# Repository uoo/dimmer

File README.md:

# dimmer
Computer controlled 24-channel dimmer

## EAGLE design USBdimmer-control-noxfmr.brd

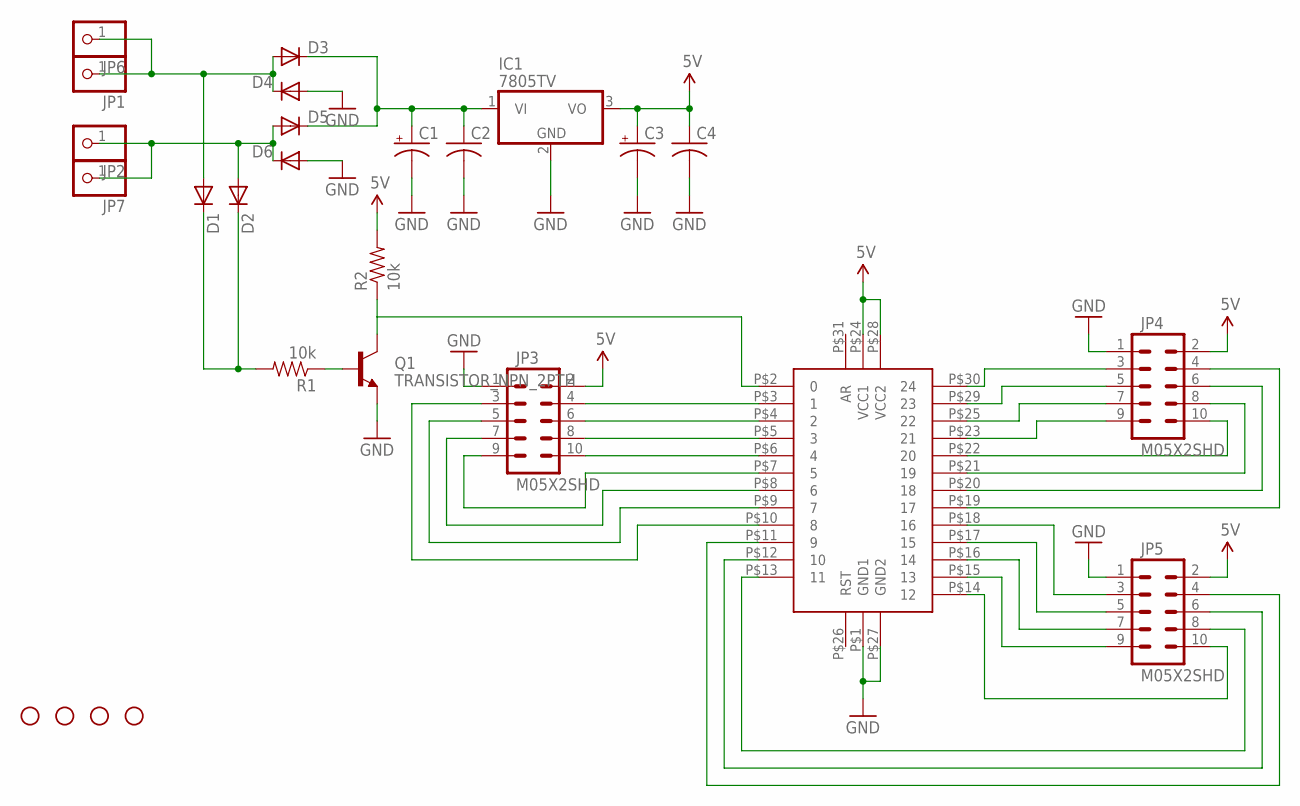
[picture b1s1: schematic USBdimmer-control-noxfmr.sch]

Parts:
C1, C3: CPOL-USE3.5-10; E3,5-10
C2, C4: C-US025-030X050; C025-030X050
D1, D2: DIODE1N4148; DIODE-1N4148
D3, D4, D5, D6: DIODEPTH; DIODE-1N4001
IC1: 7805TV; TO220V
IC2: TEENSY2
JP1, JP2, JP6, JP7: PINHD-1X1; 1X01
JP3, JP4, JP5: M05X2SHD; 2X5-SHROUDED
Q1: TRANSISTOR_NPN_2PTH; TO-92
R1, R2: 10k; AXIAL-0.4
STANDOFF1, STANDOFF2, STANDOFF3, STANDOFF4: STAND-OFF

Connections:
5V: C3.+, C4.1, IC1.3 (VO), IC2.P$24 (VCC1), IC2.P$28 (VCC2), JP3.2, JP4.2, JP5.2, R2.P$2 (2)
GND: C1.-, C2.2, C3.-, C4.2, D4.A, D6.A, IC1.2 (GND), IC2.P$1 (GND1), IC2.P$27 (GND2), JP3.1, JP4.1, JP5.1, Q1.3 (E)
unnamed: D2.A, D5.A, D6.C, JP2.1, JP7.1
unnamed: D1.A, D3.A, D4.C, JP1.1, JP6.1
unnamed: C1.+, C2.1, D3.C, D5.C, IC1.1 (VI)
unnamed: IC2.P$21 (19), JP4.8
unnamed: IC2.P$20 (18), JP4.6
unnamed: Q1.2 (B), R1.P$1 (1)
unnamed: D1.C, D2.C, R1.P$2 (2)
unnamed: IC2.P$2 (0), Q1.1 (C), R2.P$1 (1)
unnamed: IC2.P$19 (17), JP4.4
unnamed: IC2.P$18 (16), JP5.3
unnamed: IC2.P$3 (1), JP3.4
unnamed: IC2.P$4 (2), JP3.6
unnamed: IC2.P$5 (3), JP3.8
unnamed: IC2.P$6 (4), JP3.10
unnamed: IC2.P$7 (5), JP3.9
unnamed: IC2.P$8 (6), JP3.7
unnamed: IC2.P$17 (15), JP5.5
unnamed: IC2.P$16 (14), JP5.7
unnamed: IC2.P$9 (7), JP3.5
unnamed: IC2.P$10 (8), JP3.3
unnamed: IC2.P$30 (24), JP4.3
unnamed: IC2.P$15 (13), JP5.9
unnamed: IC2.P$14 (12), JP5.10
unnamed: IC2.P$29 (23), JP4.5
unnamed: IC2.P$25 (22), JP4.7
unnamed: IC2.P$23 (21), JP4.9
unnamed: IC2.P$22 (20), JP4.10
unnamed: IC2.P$13 (11), JP5.8
unnamed: IC2.P$12 (10), JP5.6
unnamed: IC2.P$11 (9), JP5.4

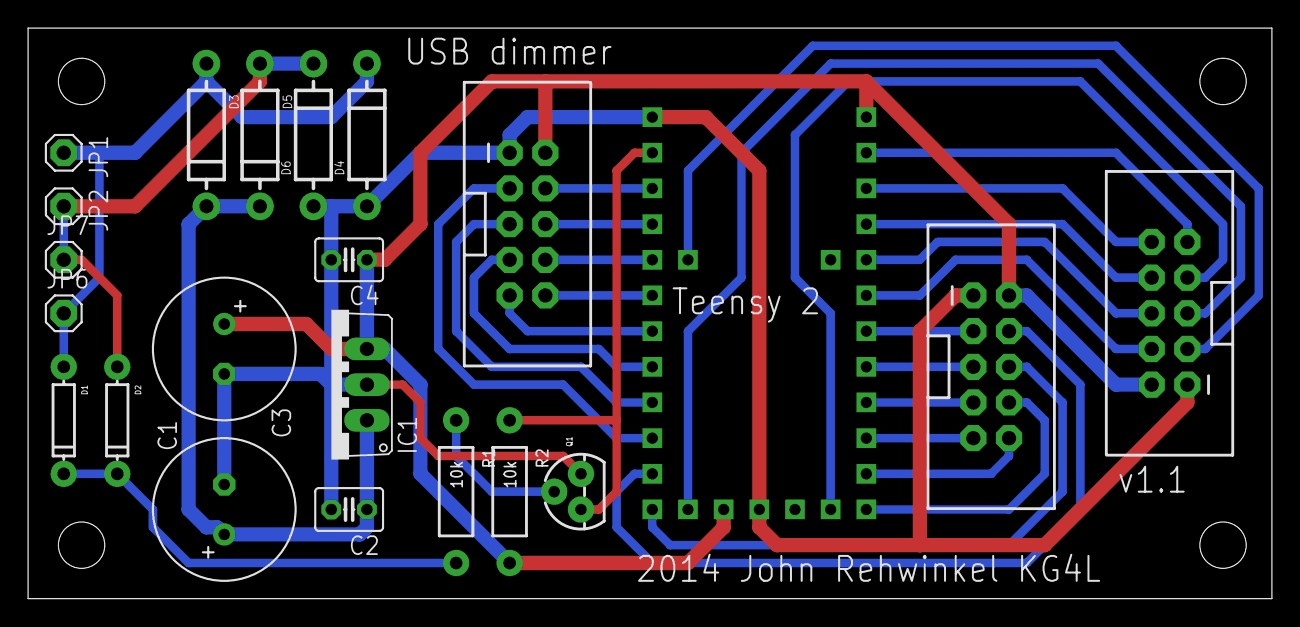
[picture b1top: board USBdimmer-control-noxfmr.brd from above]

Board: 2 copper layers, 88.6 x 40.6 mm, 26 parts (0 on the bottom side), 32 nets.

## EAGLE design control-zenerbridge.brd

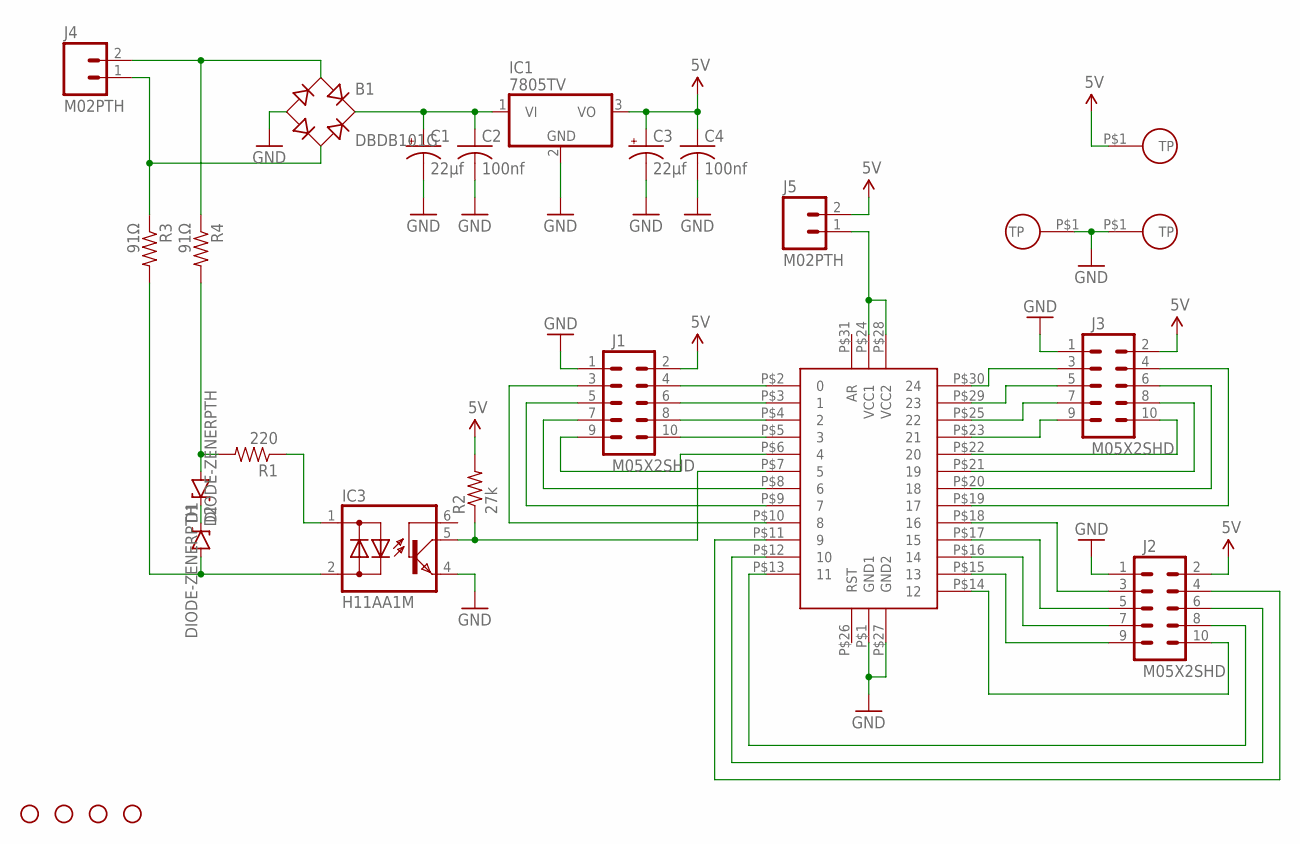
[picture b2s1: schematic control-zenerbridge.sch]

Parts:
B1: DBDB101G; DB
C1, C3: 22µf; E3,5-10
C2, C4: 100nf; C025-030X050
D1, D2: DIODE-ZENERPTH; DIODE-ZENER
IC1: 7805TV; TO220V
IC2: TEENSY2
IC3: H11AA1M; DIL06
J1, J2, J3: M05X2SHD; 2X5-SHROUDED
J4, J5: M02PTH; 1X02
R1: 220; AXIAL-0.4
R2: 27k; AXIAL-0.4
R3, R4: 91Ω; AXIAL-0.4
STANDOFF1, STANDOFF2, STANDOFF3, STANDOFF4: STAND-OFF
U$3, U$8, U$9: TP

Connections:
5V: C3.+, C4.1, IC1.3 (VO), J1.2, J2.2, J3.2, J5.2, R2.P$2 (2), U$8.P$1
GND: B1.-, C1.-, C2.2, C3.-, C4.2, IC1.2 (GND), IC2.P$1 (GND1), IC2.P$27 (GND2), IC3.4 (E), J1.1, J2.1, J3.1, U$3.P$1, U$9.P$1
unnamed: D1.P$2 (A), IC3.2 (AC2), R3.P$2 (2)
unnamed: B1.AC1, J4.2, R4.P$1 (1)
unnamed: B1.+, C1.+, C2.1, IC1.1 (VI)
unnamed: IC2.P$21 (19), J3.8
unnamed: IC2.P$20 (18), J3.6
unnamed: IC2.P$2 (0), J1.4
unnamed: IC2.P$3 (1), J1.6
unnamed: IC2.P$7 (5), IC3.5 (C), R2.P$1 (1)
unnamed: IC2.P$19 (17), J3.4
unnamed: IC2.P$18 (16), J2.3
unnamed: IC2.P$4 (2), J1.8
unnamed: IC2.P$5 (3), J1.10
unnamed: IC2.P$24 (VCC1), IC2.P$28 (VCC2), J5.1
unnamed: B1.AC2, J4.1, R3.P$1 (1)
unnamed: IC3.1 (AC1), R1.P$1 (1)
unnamed: IC2.P$6 (4), J1.9
unnamed: IC2.P$8 (6), J1.7
unnamed: D2.P$2 (A), R1.P$2 (2), R4.P$2 (2)
unnamed: IC2.P$17 (15), J2.5
unnamed: IC2.P$16 (14), J2.7
unnamed: IC2.P$9 (7), J1.5
unnamed: IC2.P$10 (8), J1.3
unnamed: IC2.P$30 (24), J3.3
unnamed: IC2.P$15 (13), J2.9
unnamed: IC2.P$14 (12), J2.10
unnamed: IC2.P$29 (23), J3.5
unnamed: IC2.P$25 (22), J3.7
unnamed: IC2.P$23 (21), J3.9
unnamed: IC2.P$22 (20), J3.10
unnamed: IC2.P$13 (11), J2.8
unnamed: IC2.P$12 (10), J2.6
unnamed: IC2.P$11 (9), J2.4
unnamed: D1.P$1 (C), D2.P$1 (C)

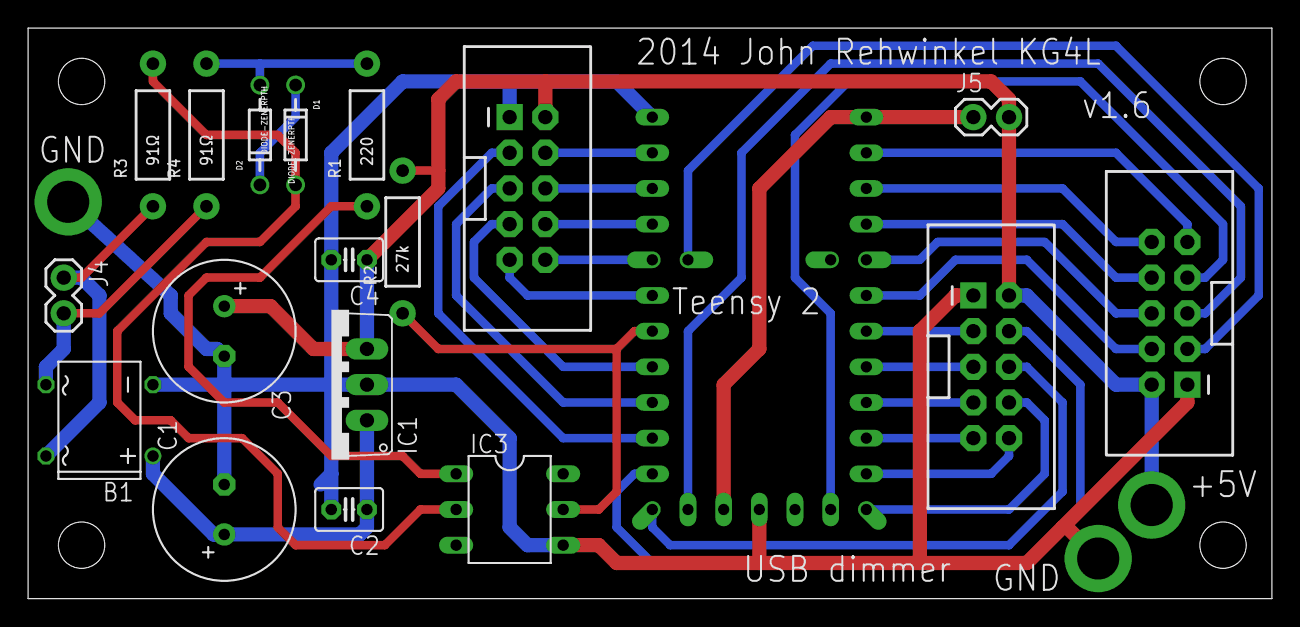
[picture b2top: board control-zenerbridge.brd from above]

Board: 2 copper layers, 88.6 x 40.6 mm, 26 parts (0 on the bottom side), 35 nets.

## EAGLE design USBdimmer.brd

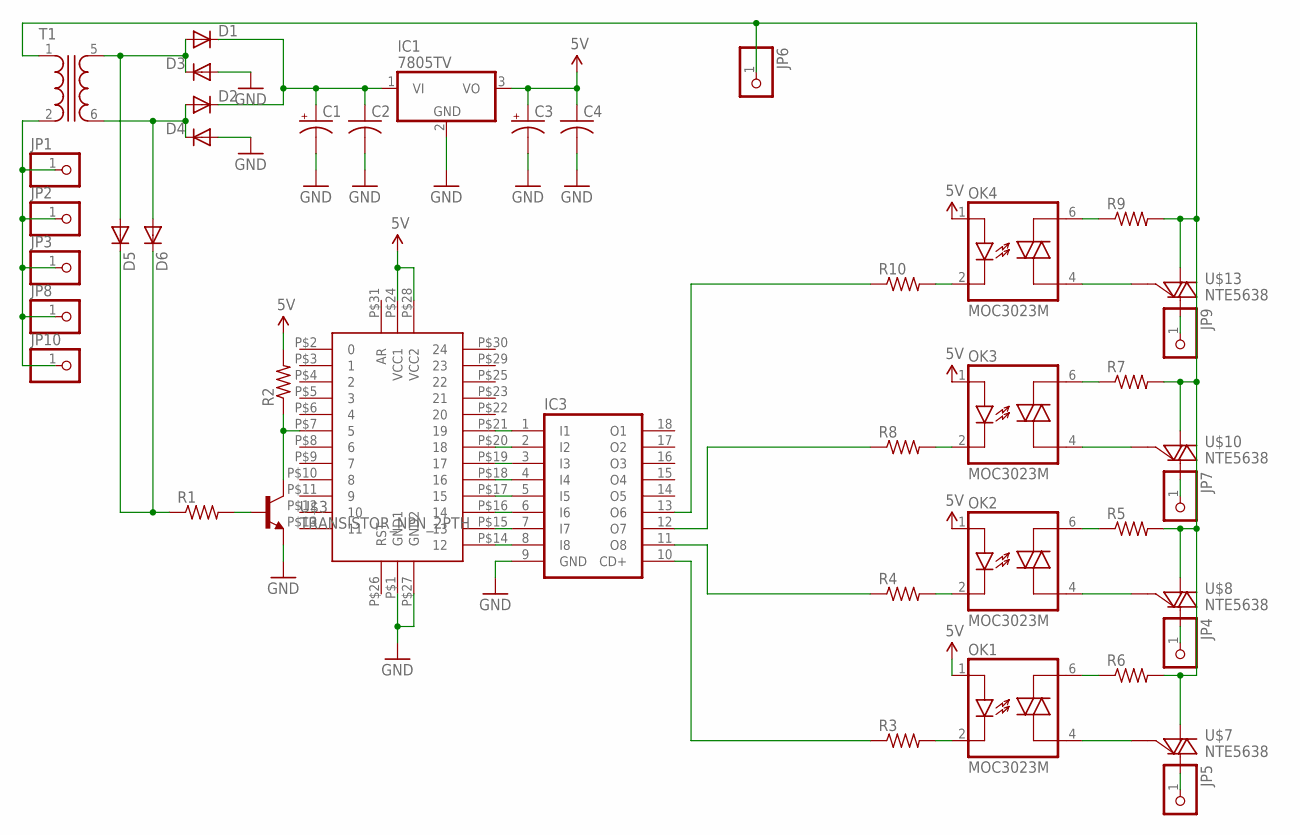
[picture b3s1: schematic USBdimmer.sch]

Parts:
C1, C3: CPOL-USE3.5-10; E3,5-10
C2, C4: C-US025-030X050; C025-030X050
D1, D2, D3, D4: DIODEPTH; DIODE-1N4001
D5, D6: DIODE1N4148; DIODE-1N4148
IC1: 7805TV; TO220V
IC3: ULN2803A; DIL18
JP1, JP2, JP3, JP4, JP5, JP6, JP7, JP8, JP9, JP10: PINHD-1X1; 1X01
OK1, OK2, OK3, OK4: MOC3023M; DIL06
R1, R2, R3, R4, R5, R6, R7, R8, R9, R10: FLIPFLOP-RES; 0805-THM
T1: XFORMER; T70-E
U$1: TEENSY2
U$3: TRANSISTOR_NPN_2PTH; TO-92
U$7, U$8, U$10, U$13: NTE5638; TO220BV

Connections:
5V: C3.+, C4.1, IC1.3 (VO), OK1.1 (A), OK2.1 (A), OK3.1 (A), OK4.1 (A), R2.2, U$1.P$24 (VCC1), U$1.P$28 (VCC2)
GND: C1.-, C2.2, C3.-, C4.2, D3.A, D4.A, IC1.2 (GND), IC3.9 (GND), U$1.P$1 (GND1), U$1.P$27 (GND2), U$3.3 (E)
unnamed: D2.A, D4.C, D6.A, T1.6 (S2)
unnamed: D1.A, D3.C, D5.A, T1.5 (S1)
unnamed: C1.+, C2.1, D1.C, D2.C, IC1.1 (VI)
unnamed: IC3.1 (I1), U$1.P$21 (19)
unnamed: IC3.2 (I2), U$1.P$20 (18)
unnamed: R1.2, U$3.2 (B)
unnamed: D5.C, D6.C, R1.1
unnamed: R2.1, U$1.P$7 (5), U$3.1 (C)
unnamed: IC3.3 (I3), U$1.P$19 (17)
unnamed: IC3.4 (I4), U$1.P$18 (16)
unnamed: JP6.1, R5.2, R6.2, R7.2, R9.2, T1.1, U$7.1 (MT1), U$8.1 (MT1), U$10.1 (MT1), U$13.1 (MT1)
unnamed: OK2.6 (MT1), R5.1
unnamed: OK2.4 (MT2), U$8.3 (G)
unnamed: JP4.1, U$8.2 (MT2)
unnamed: OK1.6 (MT1), R6.1
unnamed: OK1.4 (MT2), U$7.3 (G)
unnamed: JP5.1, U$7.2 (MT2)
unnamed: JP1.1, JP2.1, JP3.1, JP8.1, JP10.1, T1.2
unnamed: IC3.5 (I5), U$1.P$17 (15)
unnamed: IC3.6 (I6), U$1.P$16 (14)
unnamed: OK3.6 (MT1), R7.1
unnamed: OK3.4 (MT2), U$10.3 (G)
unnamed: JP7.1, U$10.2 (MT2)
unnamed: IC3.7 (I7), U$1.P$15 (13)
unnamed: IC3.8 (I8), U$1.P$14 (12)
unnamed: OK3.2 (C), R8.2
unnamed: OK2.2 (C), R4.2
unnamed: OK1.2 (C), R3.2
unnamed: OK4.6 (MT1), R9.1
unnamed: OK4.4 (MT2), U$13.3 (G)
unnamed: JP9.1, U$13.2 (MT2)
unnamed: OK4.2 (C), R10.2
unnamed: IC3.10 (CD+), R3.1
unnamed: IC3.11 (O8), R4.1
unnamed: IC3.13 (O6), R10.1
unnamed: IC3.12 (O7), R8.1

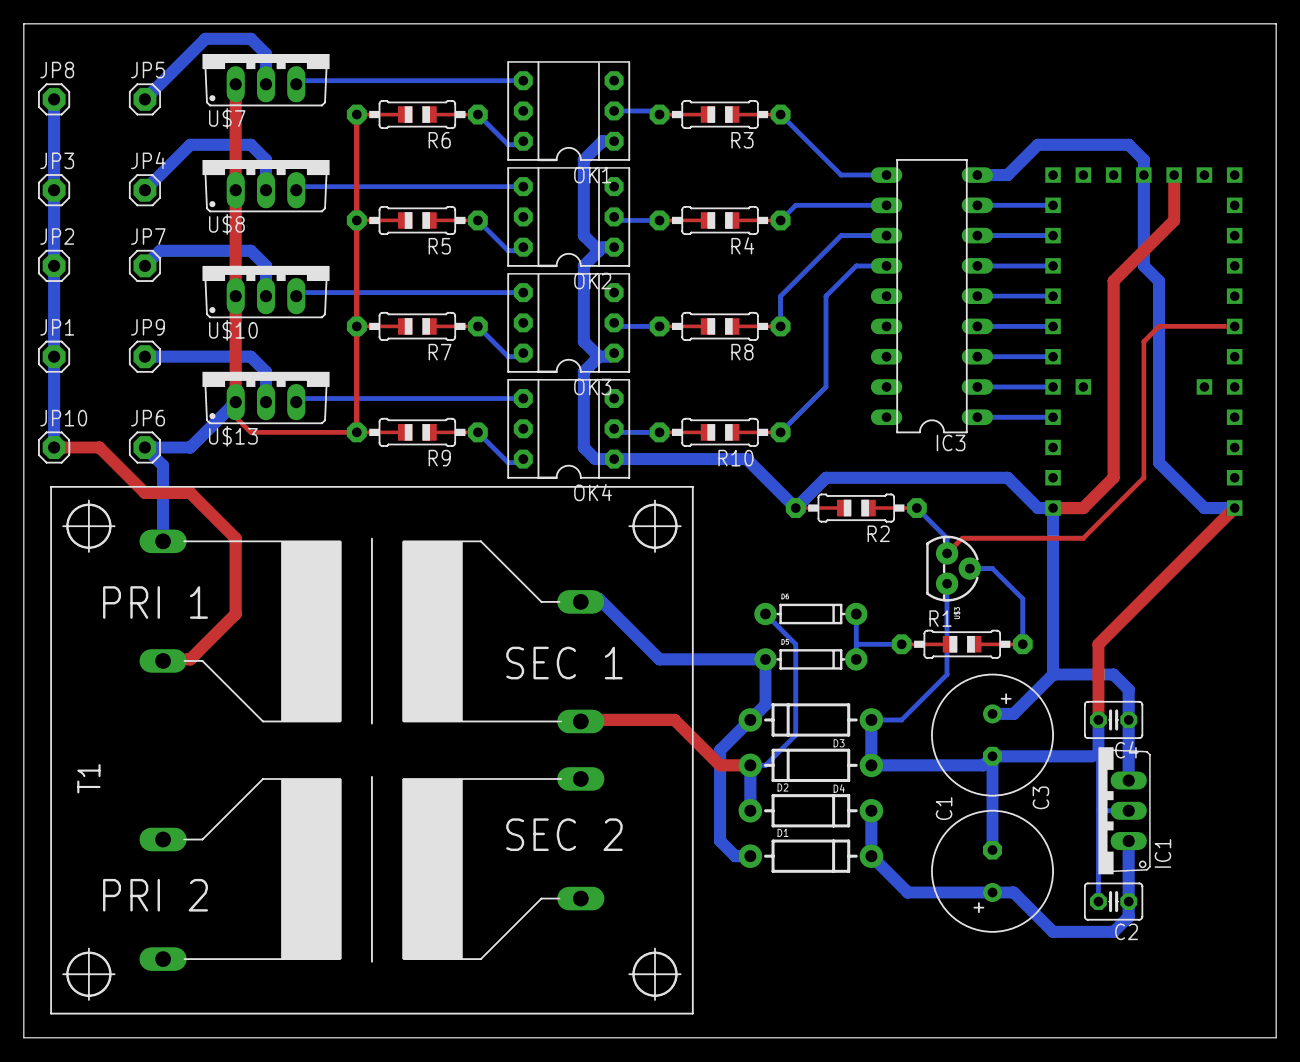
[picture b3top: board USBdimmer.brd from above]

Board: 2 copper layers, 105.1 x 85.1 mm, 43 parts (0 on the bottom side), 38 nets.

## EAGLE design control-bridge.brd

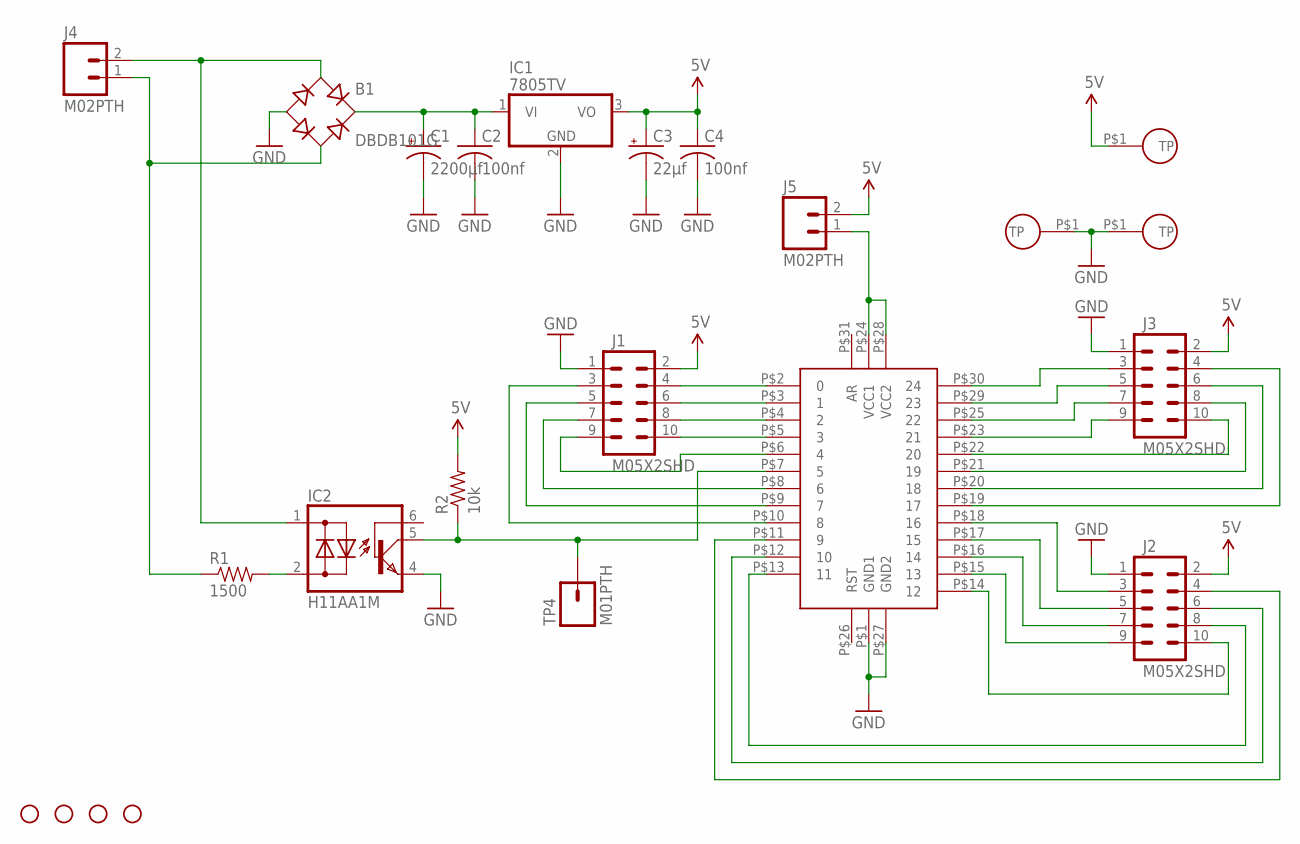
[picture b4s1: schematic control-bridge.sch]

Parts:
B1: DBDB101G; DB
C1: 2200µf; E5-13
C2, C4: 100nf; C025-030X050
C3: 22µf; E5-8,5
IC1: 7805TV; TO220V
IC2: H11AA1M; DIL06
J1, J2, J3: M05X2SHD; 2X5-SHROUDED
J4, J5: M02PTH; 1X02
R1: 1500; AXIAL-0.4
R2: 10k; AXIAL-0.4
STANDOFF1, STANDOFF2, STANDOFF3, STANDOFF4: STAND-OFF
TP1, TP2, TP3: TP
TP4: M01PTH; 1X01
U1: TEENSY2

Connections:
5V: C3.+, C4.1, IC1.3 (VO), J1.2, J2.2, J3.2, J5.2, R2.P$2 (2), TP1.P$1
GND: B1.-, C1.-, C2.2, C3.-, C4.2, IC1.2 (GND), IC2.4 (E), J1.1, J2.1, J3.1, TP2.P$1, TP3.P$1, U1.P$1 (GND1), U1.P$27 (GND2)
unnamed: B1.AC2, J4.1, R1.P$1 (1)
unnamed: B1.AC1, IC2.1 (AC1), J4.2
unnamed: B1.+, C1.+, C2.1, IC1.1 (VI)
unnamed: J3.8, U1.P$21 (19)
unnamed: J3.6, U1.P$20 (18)
unnamed: J1.4, U1.P$2 (0)
unnamed: J1.6, U1.P$3 (1)
unnamed: IC2.5 (C), R2.P$1 (1), TP4.1, U1.P$7 (5)
unnamed: J3.4, U1.P$19 (17)
unnamed: J2.3, U1.P$18 (16)
unnamed: J1.8, U1.P$4 (2)
unnamed: J1.10, U1.P$5 (3)
unnamed: J5.1, U1.P$24 (VCC1), U1.P$28 (VCC2)
unnamed: IC2.2 (AC2), R1.P$2 (2)
unnamed: J1.9, U1.P$6 (4)
unnamed: J1.7, U1.P$8 (6)
unnamed: J2.5, U1.P$17 (15)
unnamed: J2.7, U1.P$16 (14)
unnamed: J1.5, U1.P$9 (7)
unnamed: J1.3, U1.P$10 (8)
unnamed: J3.3, U1.P$30 (24)
unnamed: J2.9, U1.P$15 (13)
unnamed: J2.10, U1.P$14 (12)
unnamed: J3.5, U1.P$29 (23)
unnamed: J3.7, U1.P$25 (22)
unnamed: J3.9, U1.P$23 (21)
unnamed: J3.10, U1.P$22 (20)
unnamed: J2.8, U1.P$13 (11)
unnamed: J2.6, U1.P$12 (10)
unnamed: J2.4, U1.P$11 (9)

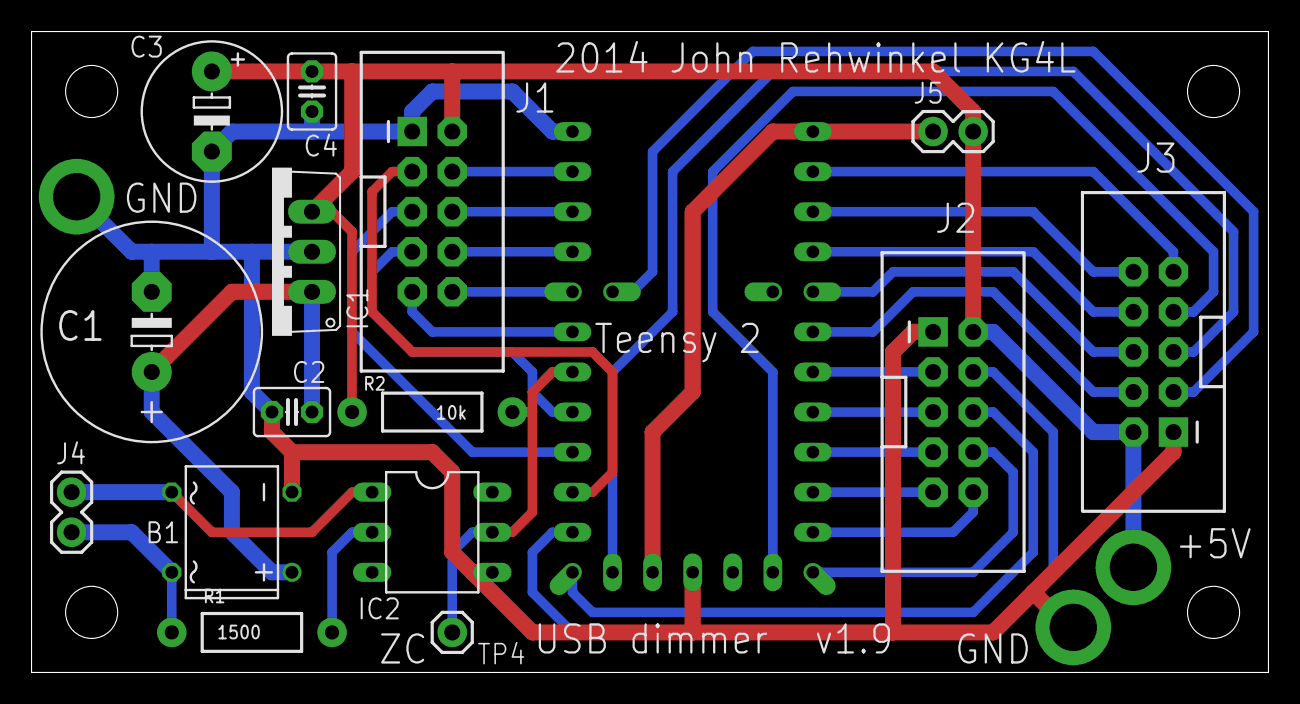
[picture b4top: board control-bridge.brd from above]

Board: 2 copper layers, 78.4 x 40.6 mm, 23 parts (0 on the bottom side), 32 nets.

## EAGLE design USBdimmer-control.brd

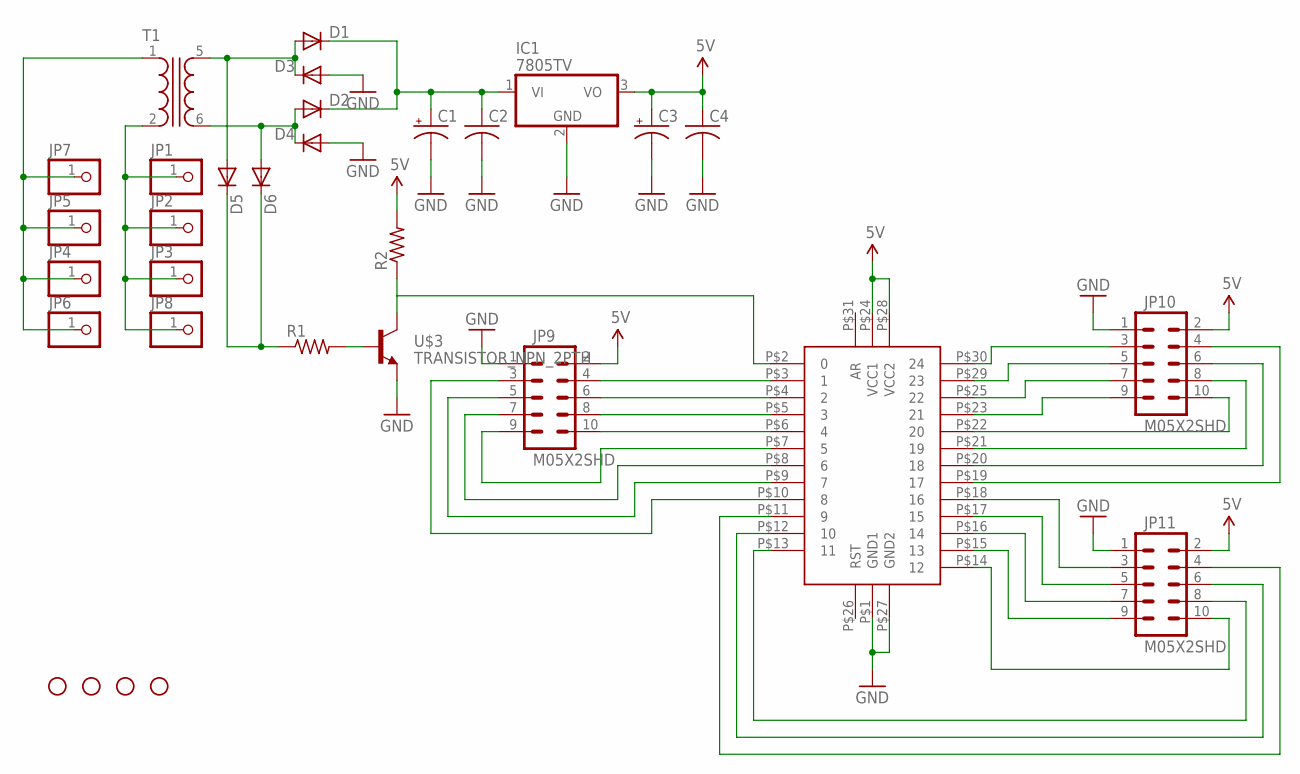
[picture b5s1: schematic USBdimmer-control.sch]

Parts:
C1, C3: CPOL-USE3.5-10; E3,5-10
C2, C4: C-US025-030X050; C025-030X050
D1, D2, D3, D4: DIODEPTH; DIODE-1N4001
D5, D6: DIODE1N4148; DIODE-1N4148
IC1: 7805TV; TO220V
JP1, JP2, JP3, JP4, JP5, JP6, JP7, JP8: PINHD-1X1; 1X01
JP9, JP10, JP11: M05X2SHD; 2X5-SHROUDED
R1, R2: FLIPFLOP-RES; 0805-THM
STANDOFF1, STANDOFF2, STANDOFF3, STANDOFF4: STAND-OFF
T1: XFORMER; T70-E
U$1: TEENSY2
U$3: TRANSISTOR_NPN_2PTH; TO-92

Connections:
5V: C3.+, C4.1, IC1.3 (VO), JP9.2, JP10.2, JP11.2, R2.2, U$1.P$24 (VCC1), U$1.P$28 (VCC2)
GND: C1.-, C2.2, C3.-, C4.2, D3.A, D4.A, IC1.2 (GND), JP9.1, JP10.1, JP11.1, U$1.P$1 (GND1), U$1.P$27 (GND2), U$3.3 (E)
unnamed: D2.A, D4.C, D6.A, T1.6 (S2)
unnamed: D1.A, D3.C, D5.A, T1.5 (S1)
unnamed: C1.+, C2.1, D1.C, D2.C, IC1.1 (VI)
unnamed: JP10.8, U$1.P$21 (19)
unnamed: JP10.6, U$1.P$20 (18)
unnamed: R1.2, U$3.2 (B)
unnamed: D5.C, D6.C, R1.1
unnamed: R2.1, U$1.P$2 (0), U$3.1 (C)
unnamed: JP10.4, U$1.P$19 (17)
unnamed: JP11.3, U$1.P$18 (16)
unnamed: JP4.1, JP5.1, JP6.1, JP7.1, T1.1
unnamed: JP9.4, U$1.P$3 (1)
unnamed: JP9.6, U$1.P$4 (2)
unnamed: JP9.8, U$1.P$5 (3)
unnamed: JP9.10, U$1.P$6 (4)
unnamed: JP9.9, U$1.P$7 (5)
unnamed: JP9.7, U$1.P$8 (6)
unnamed: JP1.1, JP2.1, JP3.1, JP8.1, T1.2
unnamed: JP11.5, U$1.P$17 (15)
unnamed: JP11.7, U$1.P$16 (14)
unnamed: JP9.5, U$1.P$9 (7)
unnamed: JP9.3, U$1.P$10 (8)
unnamed: JP10.3, U$1.P$30 (24)
unnamed: JP11.9, U$1.P$15 (13)
unnamed: JP11.10, U$1.P$14 (12)
unnamed: JP10.5, U$1.P$29 (23)
unnamed: JP10.7, U$1.P$25 (22)
unnamed: JP10.9, U$1.P$23 (21)
unnamed: JP10.10, U$1.P$22 (20)
unnamed: JP11.8, U$1.P$13 (11)
unnamed: JP11.6, U$1.P$12 (10)
unnamed: JP11.4, U$1.P$11 (9)

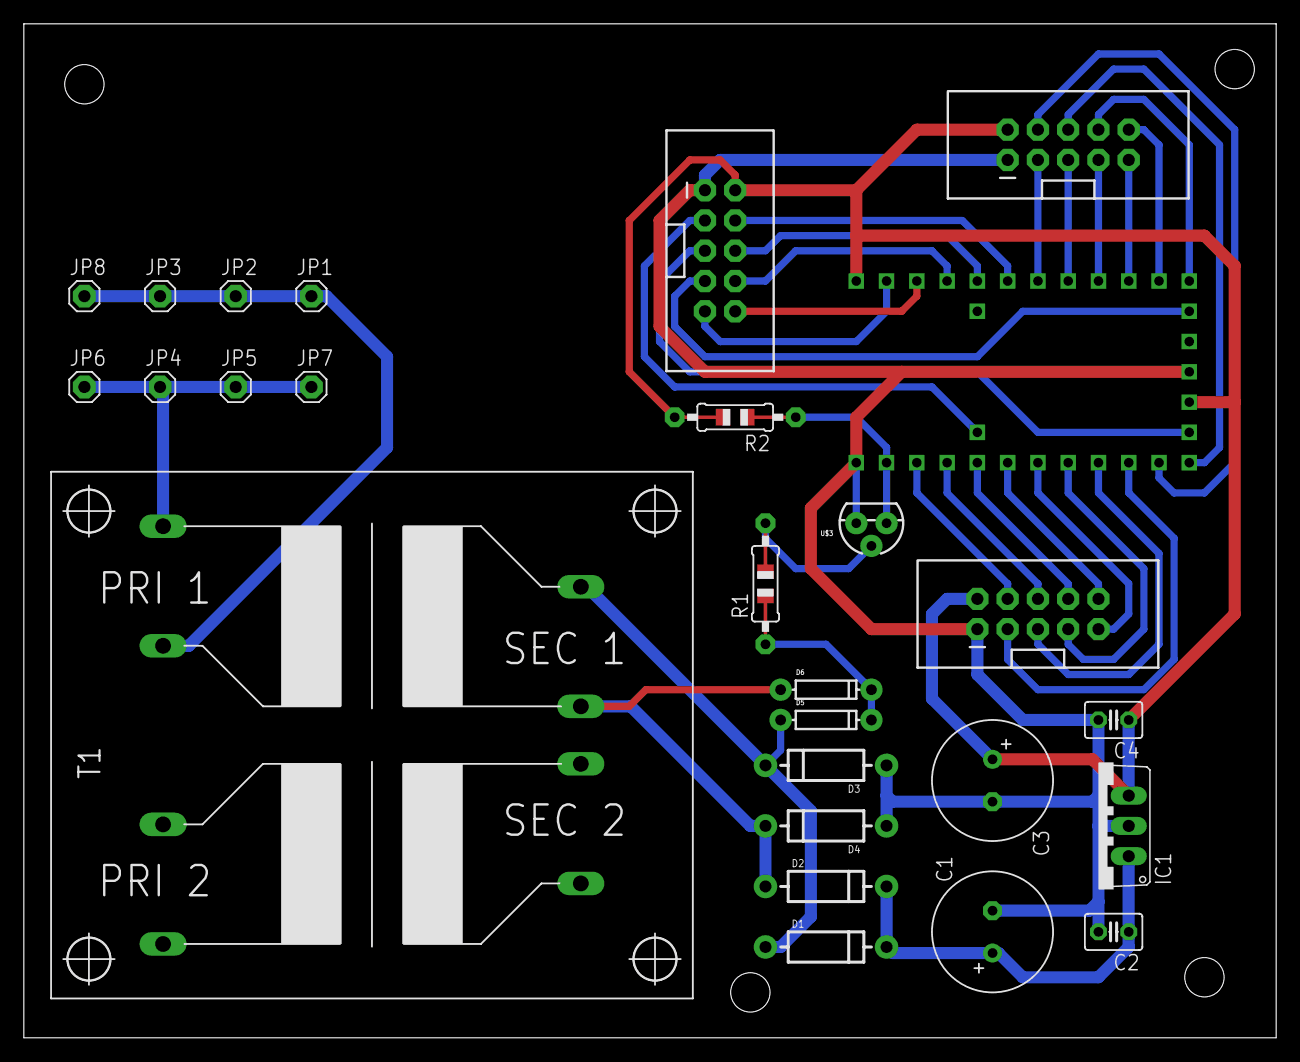
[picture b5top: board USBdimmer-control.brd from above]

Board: 2 copper layers, 105.1 x 85.1 mm, 31 parts (0 on the bottom side), 34 nets.

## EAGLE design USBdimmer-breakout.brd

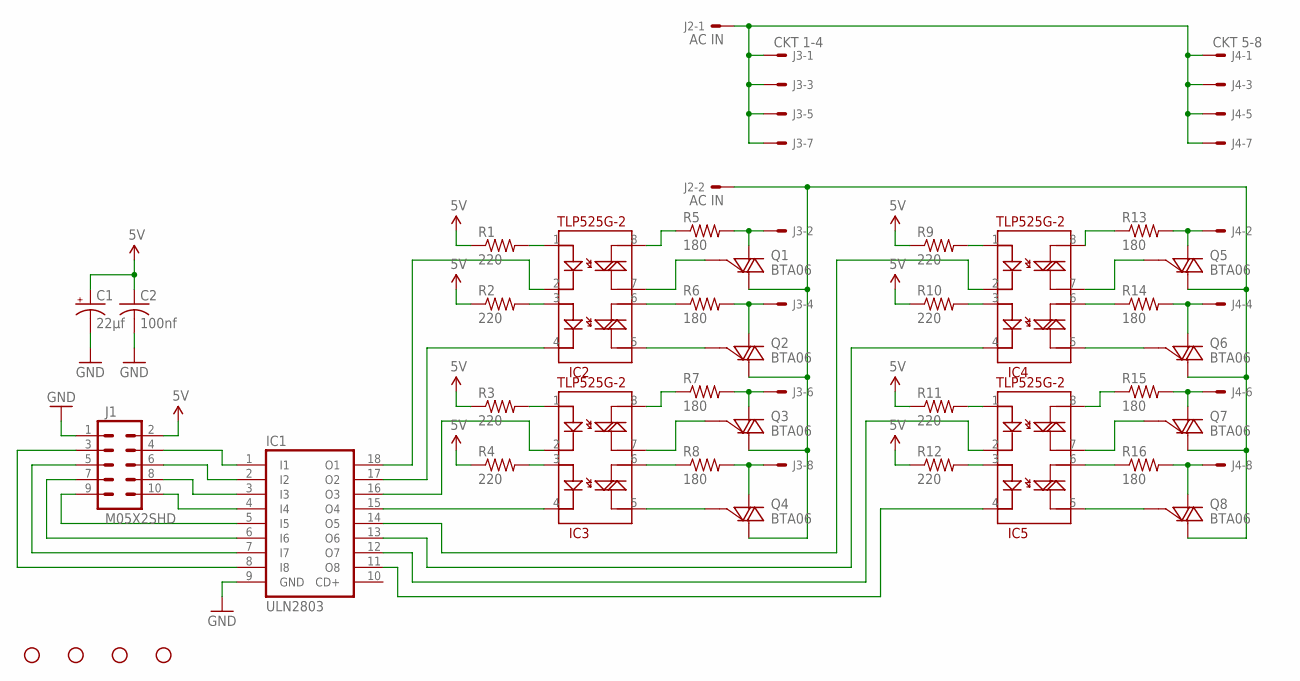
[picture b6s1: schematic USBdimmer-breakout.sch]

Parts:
C1: 22µf; E5-8,5
C2: 100nf; C025-030X050
IC1: ULN2803; DIL18
IC2, IC3, IC4, IC5: TLP525G-2; DIL08
J1: M05X2SHD; 2X5-SHROUDED
J2: AC IN; KK-156-2
J3: CKT 1-4; KK-156-8
J4: CKT 5-8; KK-156-8
Q1, Q2, Q3, Q4, Q5, Q6, Q7, Q8: BTA06; TO220BV
R1, R2, R3, R4, R9, R10, R11, R12: 220; AXIAL-0.4
R5, R6, R7, R8, R13, R14, R15, R16: 180; AXIAL-0.4
STANDOFF1, STANDOFF2, STANDOFF3, STANDOFF4: STAND-OFF

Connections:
5V: C1.+, C2.1, J1.2, R1.P$1 (1), R2.P$1 (1), R3.P$1 (1), R4.P$1 (1), R9.P$1 (1), R10.P$1 (1), R11.P$1 (1), R12.P$1 (1)
GND: C1.-, C2.2, IC1.9 (GND), J1.1
unnamed: J2.2, Q1.2 (MT2), Q2.2 (MT2), Q3.2 (MT2), Q4.2 (MT2), Q5.2 (MT2), Q6.2 (MT2), Q7.2 (MT2), Q8.2 (MT2)
unnamed: IC3.3 (A2), R4.P$2 (2)
unnamed: IC3.1 (A1), R3.P$2 (2)
unnamed: IC3.6 (MT21), R8.P$1 (1)
unnamed: IC3.5 (MT22), Q4.3 (G)
unnamed: J3.8, Q4.1 (MT1), R8.P$2 (2)
unnamed: J3.6, Q3.1 (MT1), R7.P$2 (2)
unnamed: IC3.7 (MT12), Q3.3 (G)
unnamed: IC3.8 (MT11), R7.P$1 (1)
unnamed: J3.4, Q2.1 (MT1), R6.P$2 (2)
unnamed: IC1.11 (O8), IC5.4 (K2)
unnamed: IC5.3 (A2), R12.P$2 (2)
unnamed: IC5.1 (A1), R11.P$2 (2)
unnamed: IC2.5 (MT22), Q2.3 (G)
unnamed: J3.2, Q1.1 (MT1), R5.P$2 (2)
unnamed: IC5.6 (MT21), R16.P$1 (1)
unnamed: J4.2, Q5.1 (MT1), R13.P$2 (2)
unnamed: J2.1, J3.1, J3.3, J3.5, J3.7, J4.1, J4.3, J4.5, J4.7
unnamed: J4.4, Q6.1 (MT1), R14.P$2 (2)
unnamed: IC2.3 (A2), R2.P$2 (2)
unnamed: IC5.7 (MT12), Q7.3 (G)
unnamed: IC5.8 (MT11), R15.P$1 (1)
unnamed: J4.6, Q7.1 (MT1), R15.P$2 (2)
unnamed: IC2.1 (A1), R1.P$2 (2)
unnamed: IC2.6 (MT21), R6.P$1 (1)
unnamed: IC4.5 (MT22), Q6.3 (G)
unnamed: IC4.6 (MT21), R14.P$1 (1)
unnamed: IC4.7 (MT12), Q5.3 (G)
unnamed: IC2.7 (MT12), Q1.3 (G)
unnamed: IC4.8 (MT11), R13.P$1 (1)
unnamed: IC4.1 (A1), R9.P$2 (2)
unnamed: IC5.5 (MT22), Q8.3 (G)
unnamed: IC4.3 (A2), R10.P$2 (2)
unnamed: IC2.8 (MT11), R5.P$1 (1)
unnamed: IC1.12 (O7), IC5.2 (K1)
unnamed: IC1.13 (O6), IC4.4 (K2)
unnamed: IC1.14 (O5), IC4.2 (K1)
unnamed: IC1.15 (O4), IC3.4 (K2)
unnamed: IC1.16 (O3), IC3.2 (K1)
unnamed: IC1.17 (O2), IC2.4 (K2)
unnamed: IC1.18 (O1), IC2.2 (K1)
unnamed: IC1.1 (I1), J1.4
unnamed: IC1.2 (I2), J1.6
unnamed: IC1.3 (I3), J1.8
unnamed: IC1.4 (I4), J1.10
unnamed: IC1.5 (I5), J1.9
unnamed: IC1.6 (I6), J1.7
unnamed: IC1.7 (I7), J1.5
unnamed: IC1.8 (I8), J1.3
unnamed: J4.8, Q8.1 (MT1), R16.P$2 (2)

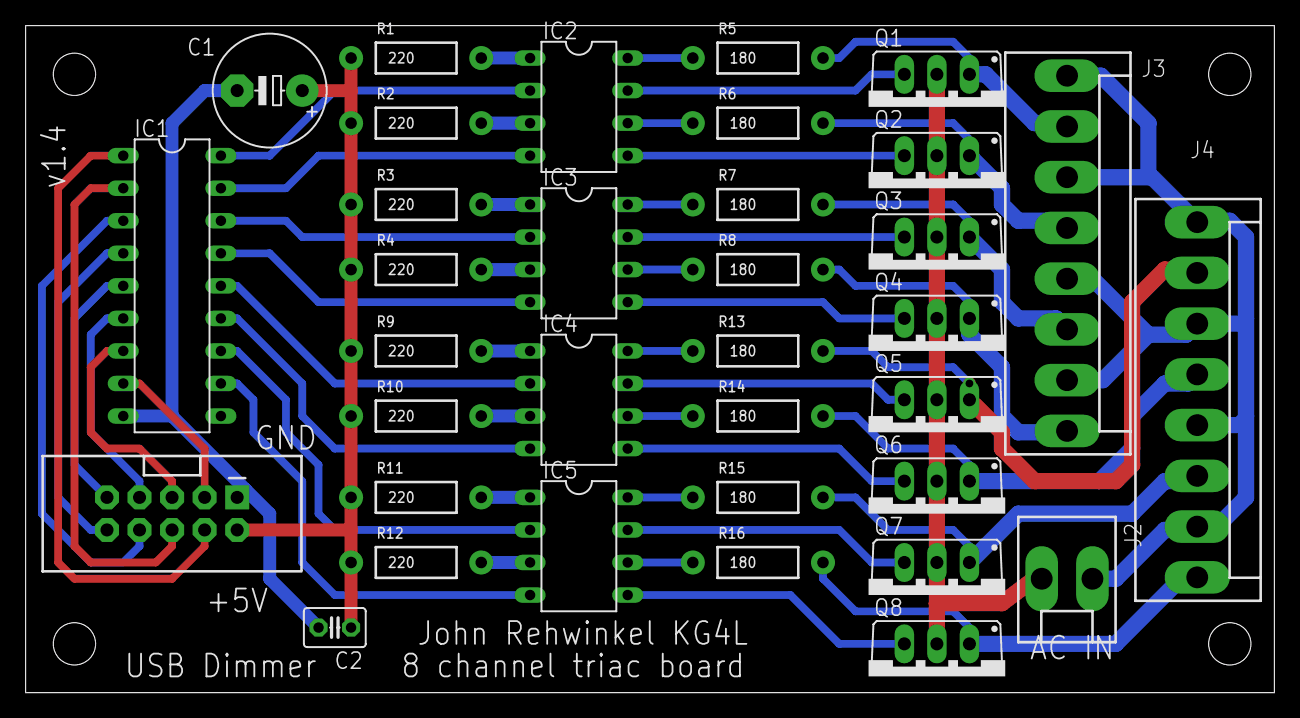
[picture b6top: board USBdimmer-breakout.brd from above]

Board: 2 copper layers, 97.5 x 52.1 mm, 39 parts (0 on the bottom side), 52 nets.

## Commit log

2015-06-08 initial checkin

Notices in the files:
parts and their libraries:
SparkFun-Electromechanical: Licensing: Creative Commons ShareAlike 4.0 International - https://creativecommons.org/licenses/by-sa/4.0
SparkFun-Aesthetics: Licensing: CC v3.0 Share-Alike You are welcome to use this library for commercial purposes.
